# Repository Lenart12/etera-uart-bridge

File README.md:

# Etera uart gpio expander

## Project Description

This project is an expander board designed to provide control for valve motors, eight relays, and the ability to measure multiple temperature sensors using the one-wire protocol. The board is implemented using KiCad PCB design software and the PCB files can be found in the `pcb` folder. The firmware for the board is developed using PlatformIO and can be found in the `pio-eub-firmware` folder. Additionally, a Python library for interfacing with the expander board is available in the `pyetera-uart-bridge` folder.

More information about the expander board, including usage instructions and examples, can be found in the [pyetera-uart-bridge/README.md](./pyetera-uart-bridge/README.md) file.

## Hardware Description

The expander board is designed to provide versatile control capabilities for various applications. It features 8 GPIO pins that can be utilized for controlling relays or other general-purpose tasks. Additionally, the board is equipped with the ability to control 4 motors, incorporating optocouplers to ensure protection and isolation of the motor control circuits.

For temperature monitoring, the board supports one-wire temperature sensors. These sensors are enhanced with an active pull-up mechanism to ensure reliable communication over long distances. Furthermore, the board includes a FET driver to improve the slew rate, which helps in reducing electromagnetic interference and improving signal integrity over long wire distances. For this purpose the standard Arduino OneWire library was modified into [OneWireFet](./pio-eub-firmware/lib/OneWireFet) which can support mastering the 1-wire bus with two uC pins. 

#### Appendix A. Improved CPU Bus Interface

> For long line applications, modifications are necessary. Appendix A shows a variant of the microprocessor port-pin attachments, i e., a FET driver with slew-rate control and a 1kΩ pullup resistor. A radius of up to 200m and a weight of up to 200m can be reliably supported using this interface.

For more detailed guidelines on setting up reliable long-line one-wire networks, you can refer to this [technical article](https://www.analog.com/en/resources/technical-articles/guidelines-for-reliable-long-line-1wire-networks.html).

## Schematic

## Circuit

## Home assistant MQTT device

## Hardware

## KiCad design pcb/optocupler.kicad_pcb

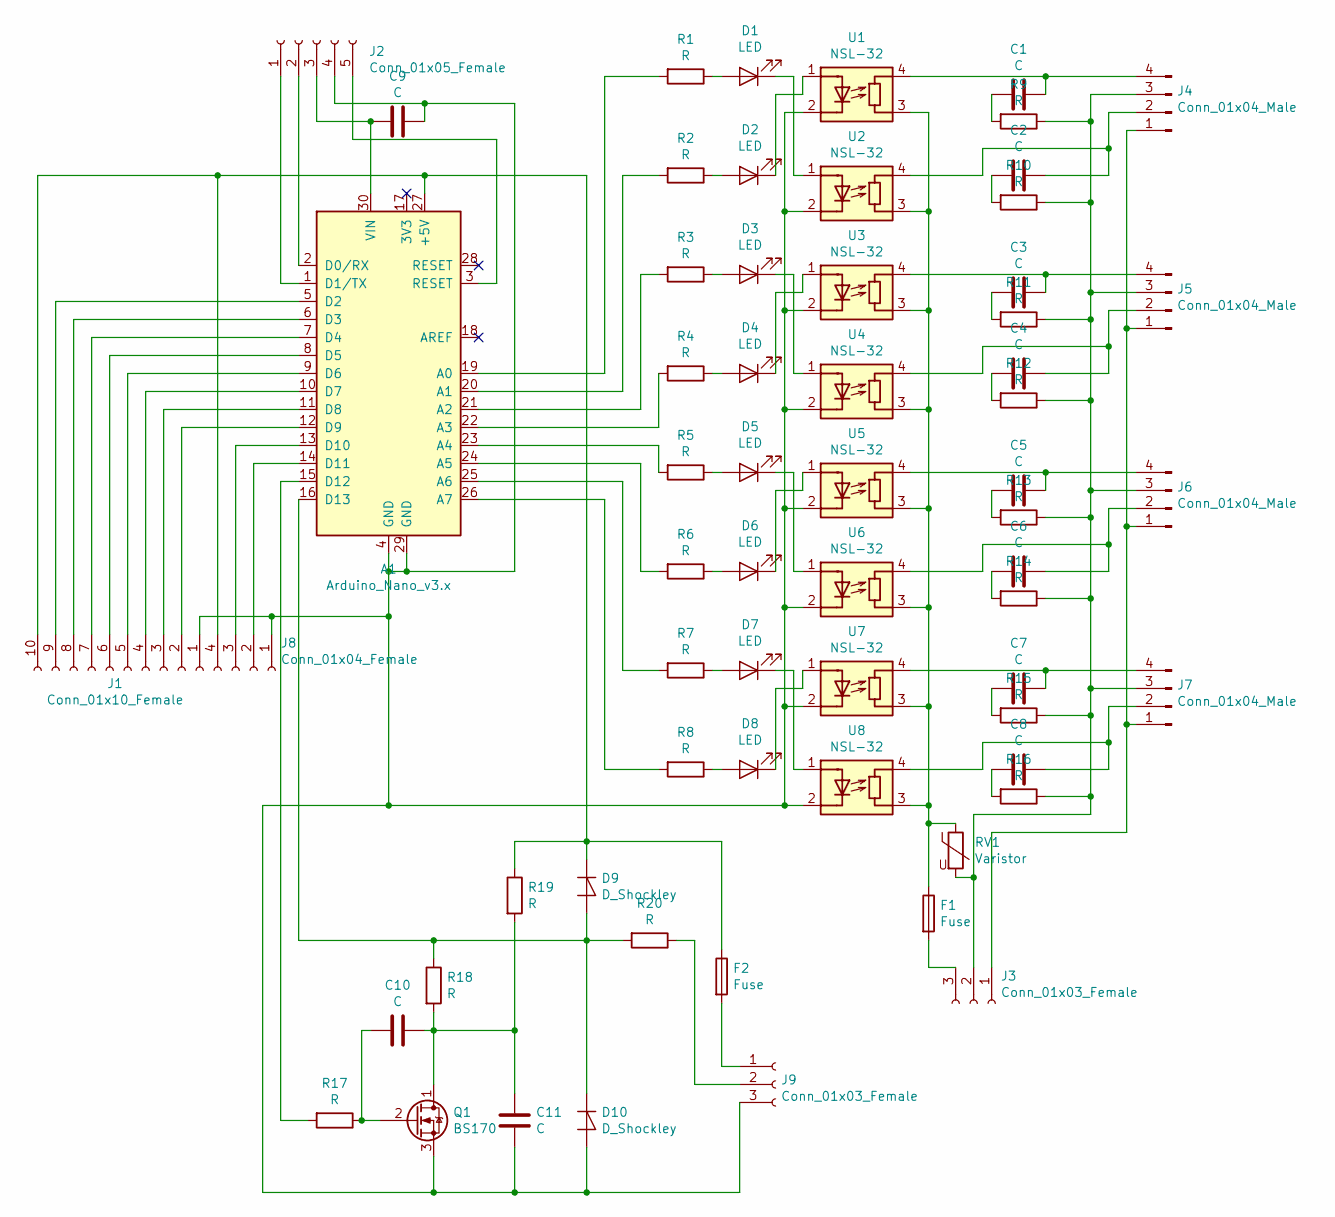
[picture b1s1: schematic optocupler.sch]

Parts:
A1: Arduino_Nano_v3.x; Arduino_Nano
C1, C2, C3, C4, C5, C6, C7, C8: C; C_Axial_L17.0mm_D6.5mm_P20.00mm_Horizontal
C9, C10, C11: C; C_Disc_D4.7mm_W2.5mm_P5.00mm
D1, D2, D3, D4, D5, D6, D7, D8: LED; LED_D5.0mm
D9, D10: D_Shockley; D_A-405_P10.16mm_Horizontal
F1, F2: Fuse; Fuseholder_Cylinder-5x20mm_Stelvio-Kontek_PTF78_Horizontal_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
J1: Conn_01x10_Female; PinSocket_1x10_P2.54mm_Vertical
J2: Conn_01x05_Female; PinSocket_1x05_P2.54mm_Vertical
J3, J9: Conn_01x03_Female; JST_NV_B03P-NV_1x03_P5.00mm_Vertical
J4, J5, J6, J7: Conn_01x04_Male; PhoenixContact_MSTBVA_2,5_4-G_1x04_P5.00mm_Vertical
J8: Conn_01x04_Female; PinSocket_1x04_P2.54mm_Vertical
Q1: BS170; TO-92_Inline
R1, R2, R3, R4, R5, R6, R7, R8, R9, R10, R11, R12, R13, R14, R15, R16, R17, R18, R19, R20: R; R_Axial_DIN0411_L9.9mm_D3.6mm_P12.70mm_Horizontal
RV1: Varistor; RV_Disc_D15.5mm_W4mm_P7.5mm
U1, U2, U3, U4, U5, U6, U7, U8: NSL-32; DIP-5-6_W7.62mm_LongPads

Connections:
unnamed: A1.1 (D1/TX), J2.1
unnamed: A1.2 (D0/RX), J2.2
unnamed: A1.3 (RESET), J2.5
unnamed: A1.5 (D2), J1.9
unnamed: A1.6 (D3), J1.8
unnamed: A1.7 (D4), J1.7
unnamed: A1.8 (D5), J1.6
unnamed: A1.9 (D6), J1.5
unnamed: A1.10 (D7), J1.4
unnamed: A1.11 (D8), J1.3
unnamed: A1.12 (D9), J1.2
unnamed: A1.13 (D10), J8.3
unnamed: A1.14 (D11), J8.2
unnamed: A1.15 (D12), R17.2
unnamed: A1.16 (D13), D9.2 (A), D10.1 (K), R18.1, R20.2
unnamed: A1.19 (A0), R1.2
unnamed: A1.20 (A1), R2.2
unnamed: A1.21 (A2), R3.2
unnamed: A1.22 (A3), R4.2
unnamed: A1.23 (A4), R5.2
unnamed: A1.24 (A5), R6.2
unnamed: A1.25 (A6), R7.2
unnamed: A1.26 (A7), R8.2
unnamed: A1.27 (+5V), D9.1 (K), F2.1, J1.10, J8.4, R19.1
unnamed: A1.4 (GND), A1.29 (GND), C9.1, C11.2, D10.2 (A), J1.1, J2.4, J8.1, J9.3, Q1.3 (S), U1.2 (K), U2.2 (K), U3.2 (K), U4.2 (K), U5.2 (K), U6.2 (K), U7.2 (K), U8.2 (K)
unnamed: A1.30 (VIN), C9.2, J2.3
unnamed: C1.1, R9.2
unnamed: C1.2, J4.4, U1.4 (R)
unnamed: C2.1, R10.2
unnamed: C2.2, J4.2, U2.4 (R)
unnamed: C3.1, R11.2
unnamed: C3.2, J5.4, U3.4 (R)
unnamed: C4.1, R12.2
unnamed: C4.2, J5.2, U4.4 (R)
unnamed: C5.1, R13.2
unnamed: C5.2, J6.4, U5.4 (R)
unnamed: C6.1, R14.2
unnamed: C6.2, J6.2, U6.4 (R)
unnamed: C7.1, R15.2
unnamed: C7.2, J7.4, U7.4 (R)
unnamed: C8.1, R16.2
unnamed: C8.2, J7.2, U8.4 (R)
unnamed: C10.1, C11.1, Q1.1 (D), R18.2, R19.2
unnamed: C10.2, Q1.2 (G), R17.1
unnamed: D1.1 (K), U2.1 (A)
unnamed: D1.2 (A), R1.1
unnamed: D2.1 (K), U1.1 (A)
unnamed: D2.2 (A), R2.1
unnamed: D3.1 (K), U4.1 (A)
unnamed: D3.2 (A), R3.1
unnamed: D4.1 (K), U3.1 (A)
unnamed: D4.2 (A), R4.1
unnamed: D5.1 (K), U6.1 (A)
unnamed: D5.2 (A), R5.1
unnamed: D6.1 (K), U5.1 (A)
unnamed: D6.2 (A), R6.1
unnamed: D7.1 (K), U8.1 (A)
unnamed: D7.2 (A), R7.1
unnamed: D8.1 (K), U7.1 (A)
unnamed: D8.2 (A), R8.1
unnamed: F1.1, RV1.1, U1.3 (R), U2.3 (R), U3.3 (R), U4.3 (R), U5.3 (R), U6.3 (R), U7.3 (R), U8.3 (R)
unnamed: F1.2, J3.3
unnamed: F2.2, J9.1
unnamed: J3.1, J4.1, J5.1, J6.1, J7.1
unnamed: J3.2, J4.3, J5.3, J6.3, J7.3, R9.1, R10.1, R11.1, R12.1, R13.1, R14.1, R15.1, R16.1, RV1.2
unnamed: J9.2, R20.1

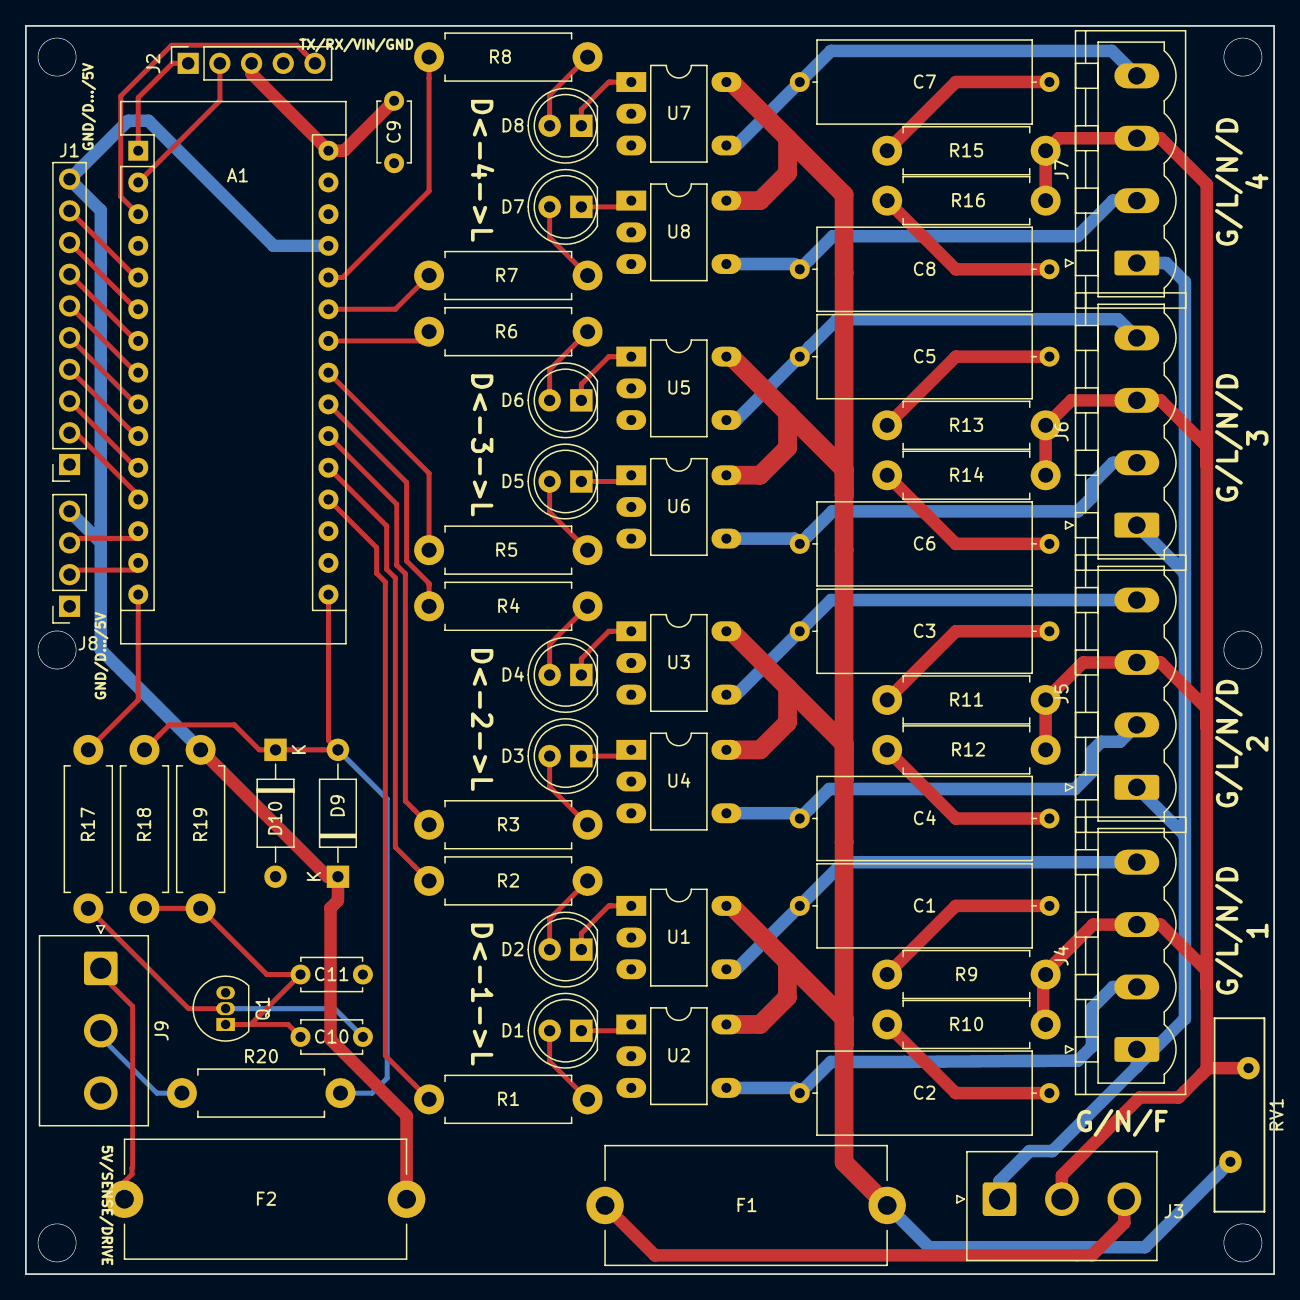
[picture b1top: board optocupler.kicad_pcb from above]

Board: 2 copper layers, 100.0 x 100.0 mm, 63 parts (0 on the bottom side), 66 nets.

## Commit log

2024-07-26 Update push tag
2024-07-26 Fix release workflow
2024-07-31 Add sensor status
2024-08-01 Add temperature reads to help
2024-08-01 Print number of sensors in setup
2024-08-01 Add reset key with r for testing in Kermit
2024-08-01 Fix typo
2024-08-02 Add example
2024-08-02 Add kronoterm2mqtt path
2024-08-10 Increase sleep in pull loop to lower the CPU load from 24% to 1%
2024-08-13 Add images
2024-08-13 pio-eub-firmware/src/TempController.cpp
2024-08-13 Increase precission read of DS1820 to 1/128 degree Celsius
2024-08-13 Images inline
2024-08-16 Do not clear LSB for other sensors
2024-09-17 Add debug temperature logs to figure out problems when sporadic xy.7[56] reading occurs.
2024-09-18 Refactor WAIT_CONVERSION state in TempController to use state delay instead of special logic
2024-09-18 Allow delay when switich states in the TempController state machine
2024-09-18 Fix whitespace
2024-09-18 Add delays to TempController state switches
2024-09-18 Set version from git tags not code
2024-09-18 Refactor release workflow to include version in artifact filenames
2024-09-20 Add switch_state for delay testing
2024-09-27 Implement .7[56] spikes filter that occour sporadicly in legacy DS1820 sensors
2024-09-27 Initialize to large positive temp so that the previous temperature reading could not be used first time in a loop
2024-09-28 Remove Direction typevfrom args due to init problems
2024-10-03 Fix double free causing a crash after TempController detects a disconnected sensor
2024-10-03 Inline images
2025-04-02 style: Fix indentation in TempController
2025-04-02 fix: Try to recover 1-wire bus instead of resetting
2025-04-02 fix: Add hard recovery timeout
2025-04-02 fix: Return 0x7FFF for invalid temperature and handle timeout in temperature reading
2025-04-02 fix: Handle invalid temperature readings in pyeub
2025-04-03 revert: Debug logging
2025-04-03 fixup: Time
2025-04-03 fixup: Syntax
2025-04-03 fixup: Debug channels
2025-04-03 fixup: Async
2025-04-03 Fixup: formatting
2025-04-03 fixup: handle pending data before sending command
2025-04-03 fixup: Read whole buffer before processing commands
2025-04-07 revert: Print addresses on boot
2025-04-08 feat: Add power state reading for devices in TempController
2025-06-04 Disable debug logging
2025-06-05 Applied .venv/bin/autopep8 --in-place --aggressive --max-line-length=119
2025-06-05 Fix f-string is missing placeholders
2025-06-05 dummy import?
2025-06-05 Code style fixes checked by flake8
2025-06-05 fix code style
2025-09-23 Code style fixes
2025-09-24 ruff format .
2026-03-27 Fix optional callable
2026-03-27 Fix optional with future
2026-03-30 Change CamelCase to python underscore to please ruff
2026-05-26 Use type hint Callable instead of built-in callable
2026-06-09 Fix callable
